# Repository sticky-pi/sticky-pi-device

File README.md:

# Hardware  and Software for the [Sticky Pi](https://sticky-pi.github.io) devices

**This readme is intended for contributors and developers**. 
Instructions to assemble Sticky Pis are available on [our documentation](https://doc.sticky-pi.com/hardware.html)

----------------------------- 

## Directory structure

### `hardware/`
Schematics, 3d files Bill of materials and such.

### `software/` 
Contains files and tools to build the Sticky Pi OS.

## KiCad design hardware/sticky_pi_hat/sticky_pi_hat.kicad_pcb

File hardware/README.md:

# Sticky Pi Hardware

* `BOM.csv` -- a bill of material containing the description of all parts used, as well as a suggestion of a provider. 
* `sticky_pi_hat/` -- One of the parts in the BOM is the Sticky Pi hat. This is our custom electronics and should be factory assembled. This directory contains the necessary KiCAD files and a BOM.
* `CAD/` -- 3d parts STL snapshots from our [Onshape repository](https://cad.onshape.com/documents/73922dc6e3c6d7006b309c14/w/7e4fb88a2e93b6adba33fd5a/e/438cef0dea4f2cfe3bf83d91)

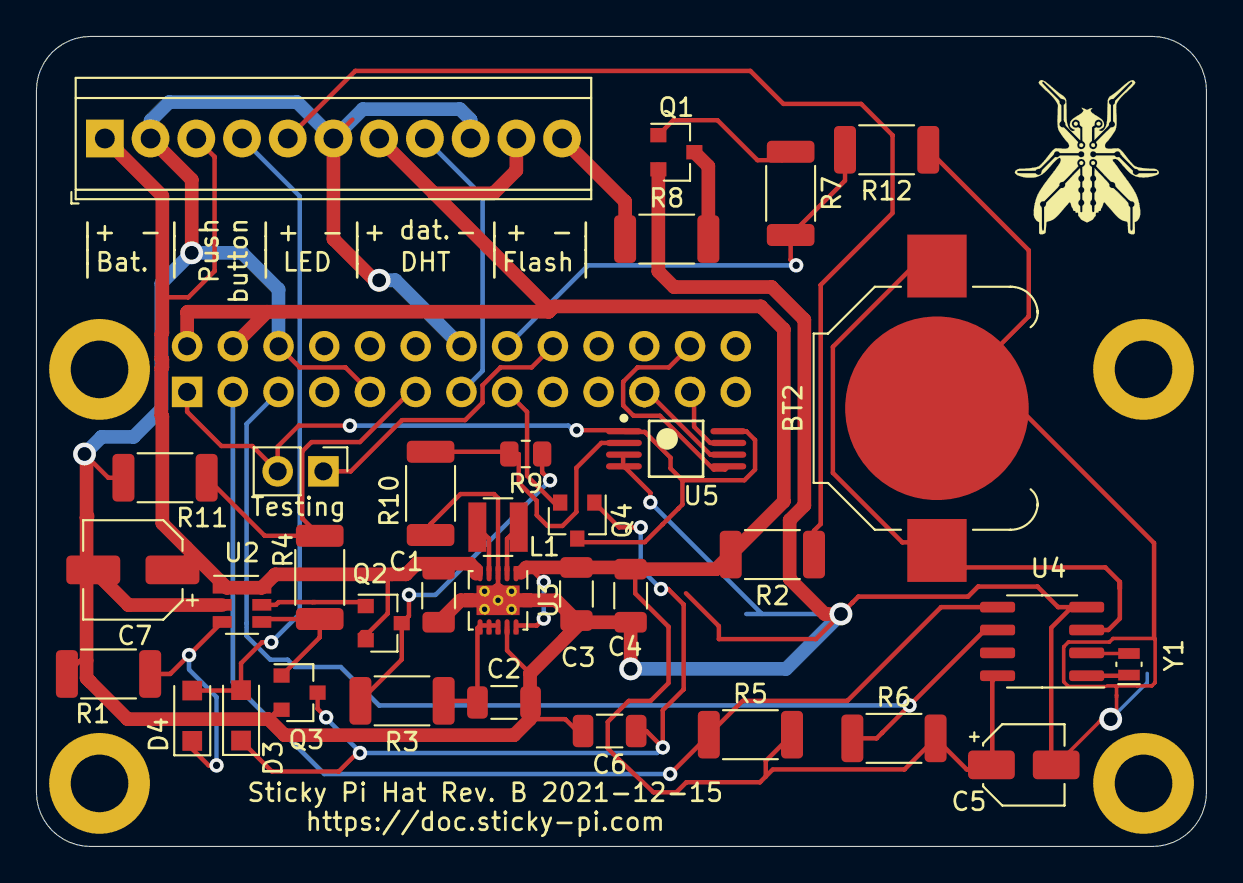
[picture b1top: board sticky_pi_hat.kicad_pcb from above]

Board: 2 copper layers, 65.0 x 45.0 mm, 35 parts (1 on the bottom side), 31 nets.

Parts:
BT2: Battery_Cell; BatteryHolder_Keystone_3000_1x12mm
C1, C3, C4, C6: 10μF; C_1206_3216Metric
C2: 0.1μF; C_1206_3216Metric
C5: 100nF; CP_Elec_4x4.5
C7: 47uF; CP_Elec_5x5.3
D3, D4: SM4001PL; D_SOD-123F
J1: Screw_Terminal_01x11; TerminalBlock_TE_1-282834-1_1x11_P2.54mm_Horizontal
J2: Conn_02x13_Odd_Even; PinSocket_2x13_P2.54mm_Vertical
J3: Conn_01x02_Male; PinHeader_1x02_P2.54mm_Vertical
L1: 2.2μH; L_Abracon_ASPI-3012S
Q1, Q3, Q4: BSS806NH6327XTSA1; SOT-23
Q2: AO3415A; SOT-23
R1, R10: 75k; R_2010_5025Metric
R2: 560Ω; R_2010_5025Metric
R3: 100Ω; R_2010_5025Metric
R4: 2.2k; R_2010_5025Metric
R5, R6, R7, R11, R12: 10k; R_2010_5025Metric
R8: 5.5Ω; R_2010_5025Metric
R9: 49.9k; R_0805_2012Metric
U2: TPL5110; SOT-23-6
U3: TPS63002; Texas_DSC0010J_ThermalVias
U4: DS1307Z+; SOIC-8_3.9x4.9mm_P1.27mm
U5: MCP3001-I_ST; Microchip-MCP3001-I_ST-Level_A
Y1: Crystal; Crystal_SMD_MicroCrystal_CM9V-T1A-2Pin_1.6x1.0mm

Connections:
+3V3: J2.1, J3.2, Q4.3, U5.1, U5.8
+5V: C3.1, C4.1, C5.1, J1.7, J1.10, J2.2, J2.4, R2.2, R5.2, R6.2, U3.1, U3.10, U4.8
+BATT: C1.1, C7.1, J1.1, J1.3, Q2.2, U2.1, U2.6, U3.5
Earth: BT2.2, C1.2, C2.1, C3.2, C4.2, C5.2, C6.2, C7.2, J1.2, J1.6, J1.9, J2.6, J2.9, J2.14, Q1.2, Q3.2, R1.2, R10.2, R11.2, R12.1, U2.2, U3.3, U3.9, U3.11, U4.4, U5.3, U5.4
GPIO_2: J2.3, R5.1, U4.5
GPIO_3: J2.5, R6.1, U4.6
GPIO_8_C0: J2.24, U5.5
GPIO_9_MISO: J2.21, U5.6
GPIO_11_clk: J2.23, U5.7
GPIO_17_R: Q3.1, R4.1, U2.4
GPIO_22: J2.15, Q4.2
GPIO_23: J2.16, R7.2, R12.2
GPIO_27: J1.8, J2.13
unnamed: BT2.1, U4.3
unnamed: C2.2, R3.1, U3.6, U3.7, U3.8
unnamed: C6.1, D3.1, Q3.3, Q4.1
unnamed: J1.11, R8.1
unnamed: J1.5, R2.1
unnamed: D4.1, R1.1, U2.3
unnamed: J2.11, R4.2, R11.1
unnamed: J2.18, J3.1
unnamed: L1.1, U3.2
unnamed: L1.2, U3.4
unnamed: Q1.1, R7.1
unnamed: Q1.3, R8.2
unnamed: R9.2, R10.1, U5.2
unnamed: U4.1, Y1.1
unnamed: U4.2, Y1.2
batt_io: Q2.3, R3.2, R9.1
drv: Q2.1, U2.5
push_button: D3.2, D4.2, J1.4

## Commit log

2020-11-04 populate device
2021-02-17 clean up BOM
2021-04-15 cleanup install script
2021-04-15 more cleanup of installation scripts
2021-04-15 almost there with refactory of device
2021-04-15 image building script ++
2021-04-15 remove legacy
2021-04-23 progress
2021-04-30 various changes for new camera, wifi harvester and packaging
2021-05-11 device++
2021-05-11 update BOM
2021-05-18 improve device firt boot script and misc
2021-09-15 new pi hat
2021-09-15 clean-up old hardware
2021-09-26 change jpeg quality to 80
2021-09-26 fix PCB issues
2021-10-02 c program to take picture
2021-10-02 more cleanup of raspistill
2021-10-02 flash and filename work
2021-10-03 reimplement dht functionality
2021-10-14 Add P-channel mosfet to tpl5110
2021-10-14 c-code ++
2021-10-30 exif metadata
2021-11-03 metadata++
2021-11-05 more work on software
2021-12-15 add external pull down resistor to flash and push button outputs
2021-12-15 improve testing routine and mcp3001 interface
2021-12-16 add diode to prevent wrong measurement of R1(timing) dut to pushbutton state holder
2022-01-21 work on sync
2022-02-04 hardware updates
2022-03-04 optional wpa setup to get time from net on first boot, in case harvester is absent
2022-03-04 cleanup
2022-03-09 update gitignore
2022-03-09 minor bug in sync tool, when harvester is absent
2022-03-30 device wifi update
2022-03-30 add deps
2022-03-31 add mock device status
2022-04-16 performance improvements: wpa, disk
2022-04-18 simpler, more effiecient http server
2022-04-18 simpler, more effiecient http server2
2022-04-19 much progress on device
2022-05-06 improve first boot and testing routine
2022-05-11 fix bug when no space is left on device. Fix bug when adding several persistent ssid with the same name
2022-05-13 shorten exif metadata field names and add failsafe
2022-05-20 fix buffer overflow in the DHT22 reading code
2022-05-31 reduce image sharpness for QR code!
2022-06-01 faster and more robust network setup fixes #10
2022-06-01 concatenate all wpa_supplicant config files, multiple does not seem to work
2022-06-02 README updates
2022-06-02 update CAD
2022-07-31 bom update
2022-07-31 readmes
2022-07-31 mock server to test deta harvesting without a device
2022-07-31 permissions update onb os stub files
